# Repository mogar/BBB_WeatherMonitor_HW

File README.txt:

These are the hardware design files for a BBB Cape that monitors weather conditions.

See also this repo for example code:

These hardware files were created with KiCAD. You may need the KiCAD libraries available here: https://github.com/mogar/KiCAD_libs When opening these projects in KiCAD, you may need to change the path to the libraries from the above link. This can be done in preferences->libraries in both the schematic editor and the layout editor. Make sure the libraries noted there point to wherever you put the above KiCAD_libs repo.

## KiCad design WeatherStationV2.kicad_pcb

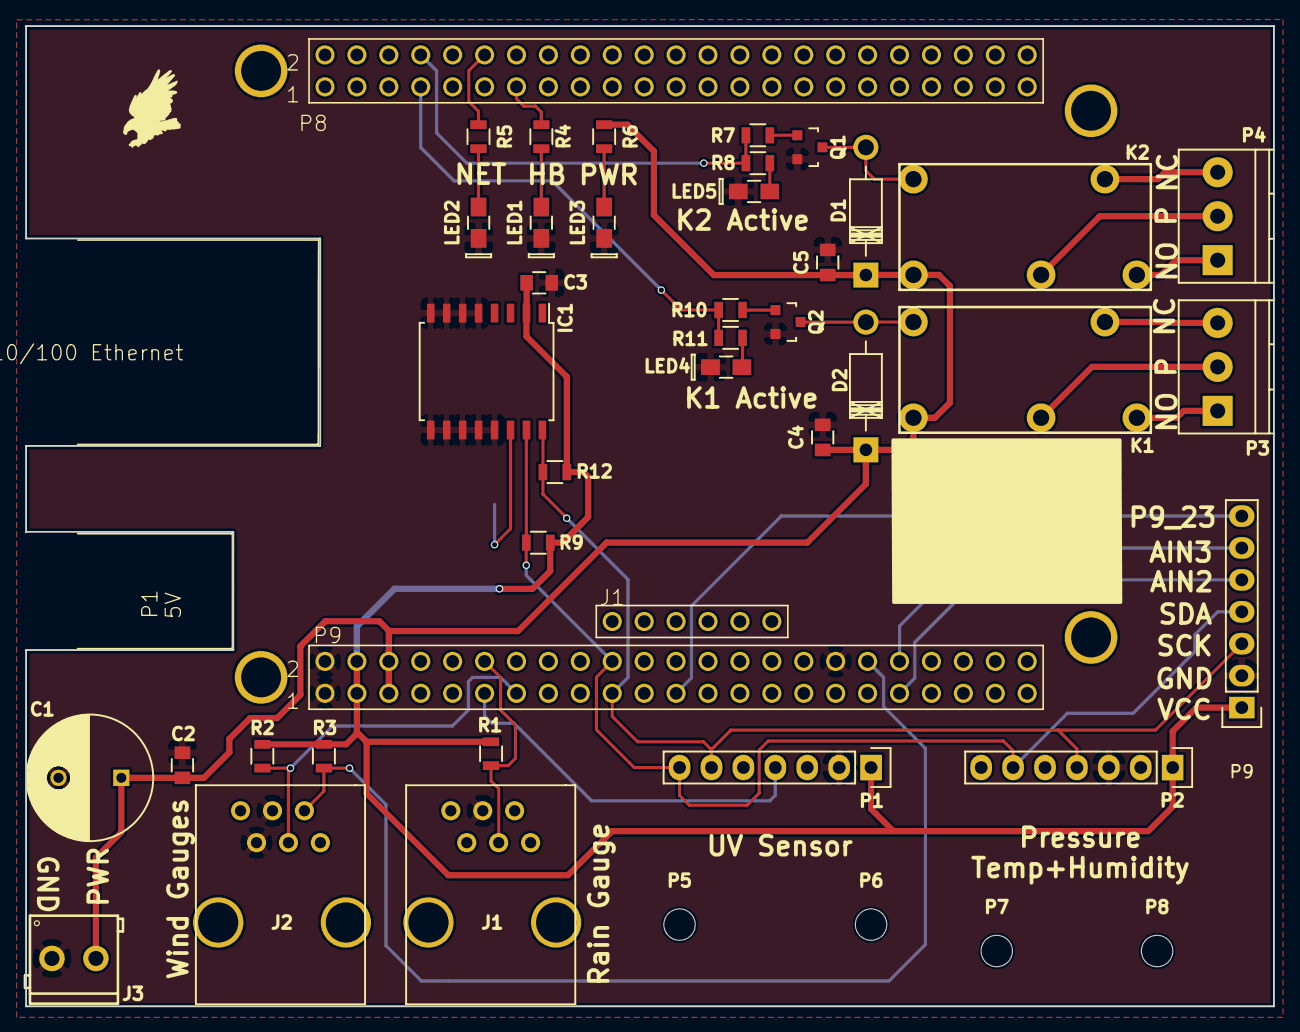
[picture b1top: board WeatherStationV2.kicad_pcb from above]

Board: 2 copper layers, 99.3 x 78.0 mm, 43 parts (0 on the bottom side), 32 nets.

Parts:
BAT1: BATTCON_20MM
C1: 470u; C_Radial_D10_L16_P5
C2: 10u; C_0805
C3, C4, C5: 1u; C_0805
D1: 1N4004; Diode_DO-41_SOD81_Horizontal_RM10
D2: 1n4004; Diode_DO-41_SOD81_Horizontal_RM10
IC1: DS3231/SO; SOIC-16_7.5x10.3mm_Pitch1.27mm
J1, J2: A-2014-1-4-R; RJ12-A-2014-1-4-R
J3: 1X2-3.5MM; SparkFun-SCREWTERMINAL-3.5MM-2
K1, K2: PB890-ND; RELAY-TE-1FORMC
LED1, LED2, LED3, LED4, LED5: LED; 0805P-HandSoldering
P1, P2, P9: CONN_01X07; Pin_Header_Straight_1x07
P3, P4: CONN_01X03; TerminalBlock_Pheonix_PT-3.5mm_3pol
P5, P6, P7, P8: CONN_01X01; MountingHole_2.5mm
PCB1: E14_BEAGLEBONEBLACK_REVA_BEAGLEBONE_BLACK; BEAGLEBONE_BLACK
Q1, Q2: MMBT3904; SOT-23
R1, R9, R12: 2.2k; R_0805
R2, R3: 10k; R_0805
R4, R5, R6, R7, R8, R10, R11: 1k; R_0805

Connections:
+3V3: C3.1, IC1.2, P1.1, P2.1, P9.1, PCB1.9_3, PCB1.9_4, R1.2, R2.2, R3.2, R9.2, R12.2
+5V: C1.1, C2.1, C4.1, C5.1, D1.1, D2.1, J3.2, K1.5, K2.5, PCB1.9_5, PCB1.9_6, R6.1
/AIN2: P9.5, PCB1.9_37
/AIN3: P9.6, PCB1.9_38
/HB_LED: PCB1.8_13, R4.1
/I2C_SCK: IC1.16, P1.6, P2.4, P9.3, PCB1.9_19, R12.1
/I2C_SDA: IC1.15, P1.7, P2.6, P9.4, PCB1.9_20, R9.1
/K1_NC: K1.4, P3.3
/K1_NO: K1.3, P3.1
/K1_P: K1.2, P3.2
/K2_NC: K2.4, P4.3
/K2_NO: K2.3, P4.1
/K2_P: K2.2, P4.2
/NET_LED: PCB1.8_12, R5.1
/P9_23: P9.7, PCB1.9_23
/RAIN_SW: J1.4, PCB1.9_12, R1.1
/RELAY1: PCB1.8_7, R10.1, R11.1
/RELAY2: PCB1.8_8, R7.1, R8.1
/UV_Int: P1.4, PCB1.9_11
/WIND_DIR: J2.5, PCB1.9_36, R3.1
/WIND_SP: J2.4, PCB1.9_13, R2.1
GND: BAT1.2, C1.2, C2.2, C3.2, C4.2, C5.2, IC1.5, IC1.6, IC1.7, IC1.8, IC1.9, IC1.10, IC1.11, IC1.12, IC1.13, J1.3, J2.2, J2.3, J3.1, LED1.1, LED2.1, LED3.1, LED4.1, LED5.1, P1.2, P2.3, P9.2, PCB1.9_1, PCB1.9_2, PCB1.9_34, Q1.2, Q2.2
unnamed: BAT1.1, IC1.14
unnamed: D1.2, K2.1, Q1.3
unnamed: D2.2, K1.1, Q2.3
unnamed: LED1.2, R4.2
unnamed: LED2.2, R5.2
unnamed: LED3.2, R6.2
unnamed: LED4.2, R11.2
unnamed: LED5.2, R8.2
unnamed: Q1.1, R7.2
unnamed: Q2.1, R10.2

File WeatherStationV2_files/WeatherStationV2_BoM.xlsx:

Id | Designator | Package | Quantity | Order Qty | Designation | Supplier | Ref | Unit Cost | Ext Cost
1 | K2,K1 | RELAY-TE-1FORMC | 2 | 32 | PB890-ND | DigiKey | PB890-ND | 1.87 | 3.74
2 | R2,R3 | R_0805 | 2 | 32 | 10k | DigiKey | RMCF0805JT10K0CT-ND | 8.8000000000000005E-3 | 1.7600000000000001E-2
3 | R4,R5,R6,R7,R8,R10,R11 | R_0805 | 7 | 112 | 1k | DigiKey | 311-1.0KARCT-ND | 7.3000000000000001E-3 | 5.11E-2
4 | IC1 | SOIC-16_7.5x10.3mm_Pitch1.27mm | 1 | 16 | DS3231/SO | DigiKey | DS3231S#T&RCT-ND | 8.1859999999999999 | 8.1859999999999999
5 | R1,R9,R12 | R_0805 | 3 | 48 | 2.2k | DigiKey | RMCF0805JT2K20CT-ND | 8.8000000000000005E-3 | 2.64E-2
6 | BAT1 | BATTCON_20MM | 1 | 16 | ~ | DigiKey | BAT-HLD-001-ND | 0.25679999999999997 | 0.25679999999999997
7 | P1,P2 | Pin_Header_Straight_1x07 | 2 | 32 | CONN_01X07 | DigiKey | S7005-ND | 0.60499999999999998 | 1.21
8 | P3,P4 | TerminalBlock_Pheonix_PT-3.5mm_3pol | 2 | 32 | CONN_01X03 | DigiKey | 277-1722-ND | 0.58699999999999997 | 1.1739999999999999
9 | C1 | C_Radial_D10_L16_P5 | 1 | 16 | 470u | DigiKey | 493-5898-1-ND | 0.22700000000000001 | 0.22700000000000001
10 | C3,C4,C5 | C_0805 | 3 | 48 | 1u | DigiKey | 311-1365-1-ND | 3.1800000000000002E-2 | 9.5400000000000013E-2
11 | D1,D2 | Diode_DO-41_SOD81_Horizontal_RM10 | 1 | 16 | 1N4004 | DigiKey | 1N4004DICT-ND | 0.115 | 0.115
12 | J3 | SparkFun-SCREWTERMINAL-3.5MM-2 | 1 | 16 | 1X2-3.5MM | DigiKey | 277-1721-ND | 0.39100000000000001 | 0.39100000000000001
13 | Q1,Q2 | SOT-23 | 2 | 32 | MMBT3904 | DigiKey | MMBT3904FSCT-ND | 0.14199999999999999 | 0.28399999999999997
14 | C2 | C_0805 | 1 | 16 | 10u | DigiKey | 490-1718-1-ND | 3.56E-2 | 3.56E-2
15 | LED1,LED2,LED3,LED4,LED5 | 0805P-HandSoldering | 5 | 80 | LED | DigiKey | 67-1557-1-ND | 0.32800000000000001 | 1.6400000000000001
16 | J1,J2 | RJ12-A-2014-1-4-R | 2 | 32 | A-2014-1-4-R | DigiKey | AE10391-ND | 0.61499999999999999 | 1.23
17 | PCB1 | BEAGLEBONE_BLACK | 1 | 16 | E14_BEAGLEBONEBLACK_REVA_BEAGLEBONE_BLACK | AdaFruit | BBB revC | 55 | 55
18 | PCB2 | Cape | 1 | 16 |  | OSHPark |  | 20 | 20
19 |  | Temp/Press/Humidity | 1 | 16 |  | AdaFruit | bme280 | 19.95 | 19.95
20 |  | UV Sensor | 1 | 16 |  | AdaFruit | si1145 | 9.9499999999999993 | 9.9499999999999993
 |  |  |  |  |  |  |  |  | 123.57990000000001

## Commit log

2016-08-22 first commit, hw tested
